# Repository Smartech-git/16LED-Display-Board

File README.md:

# 16LED-Display-Board
16 LEDs display board with 74HC595 SIPO SOIC chips. The two chips are daisy-chained, in effect a plug in and play, creating your electronics art with 16LEDs.

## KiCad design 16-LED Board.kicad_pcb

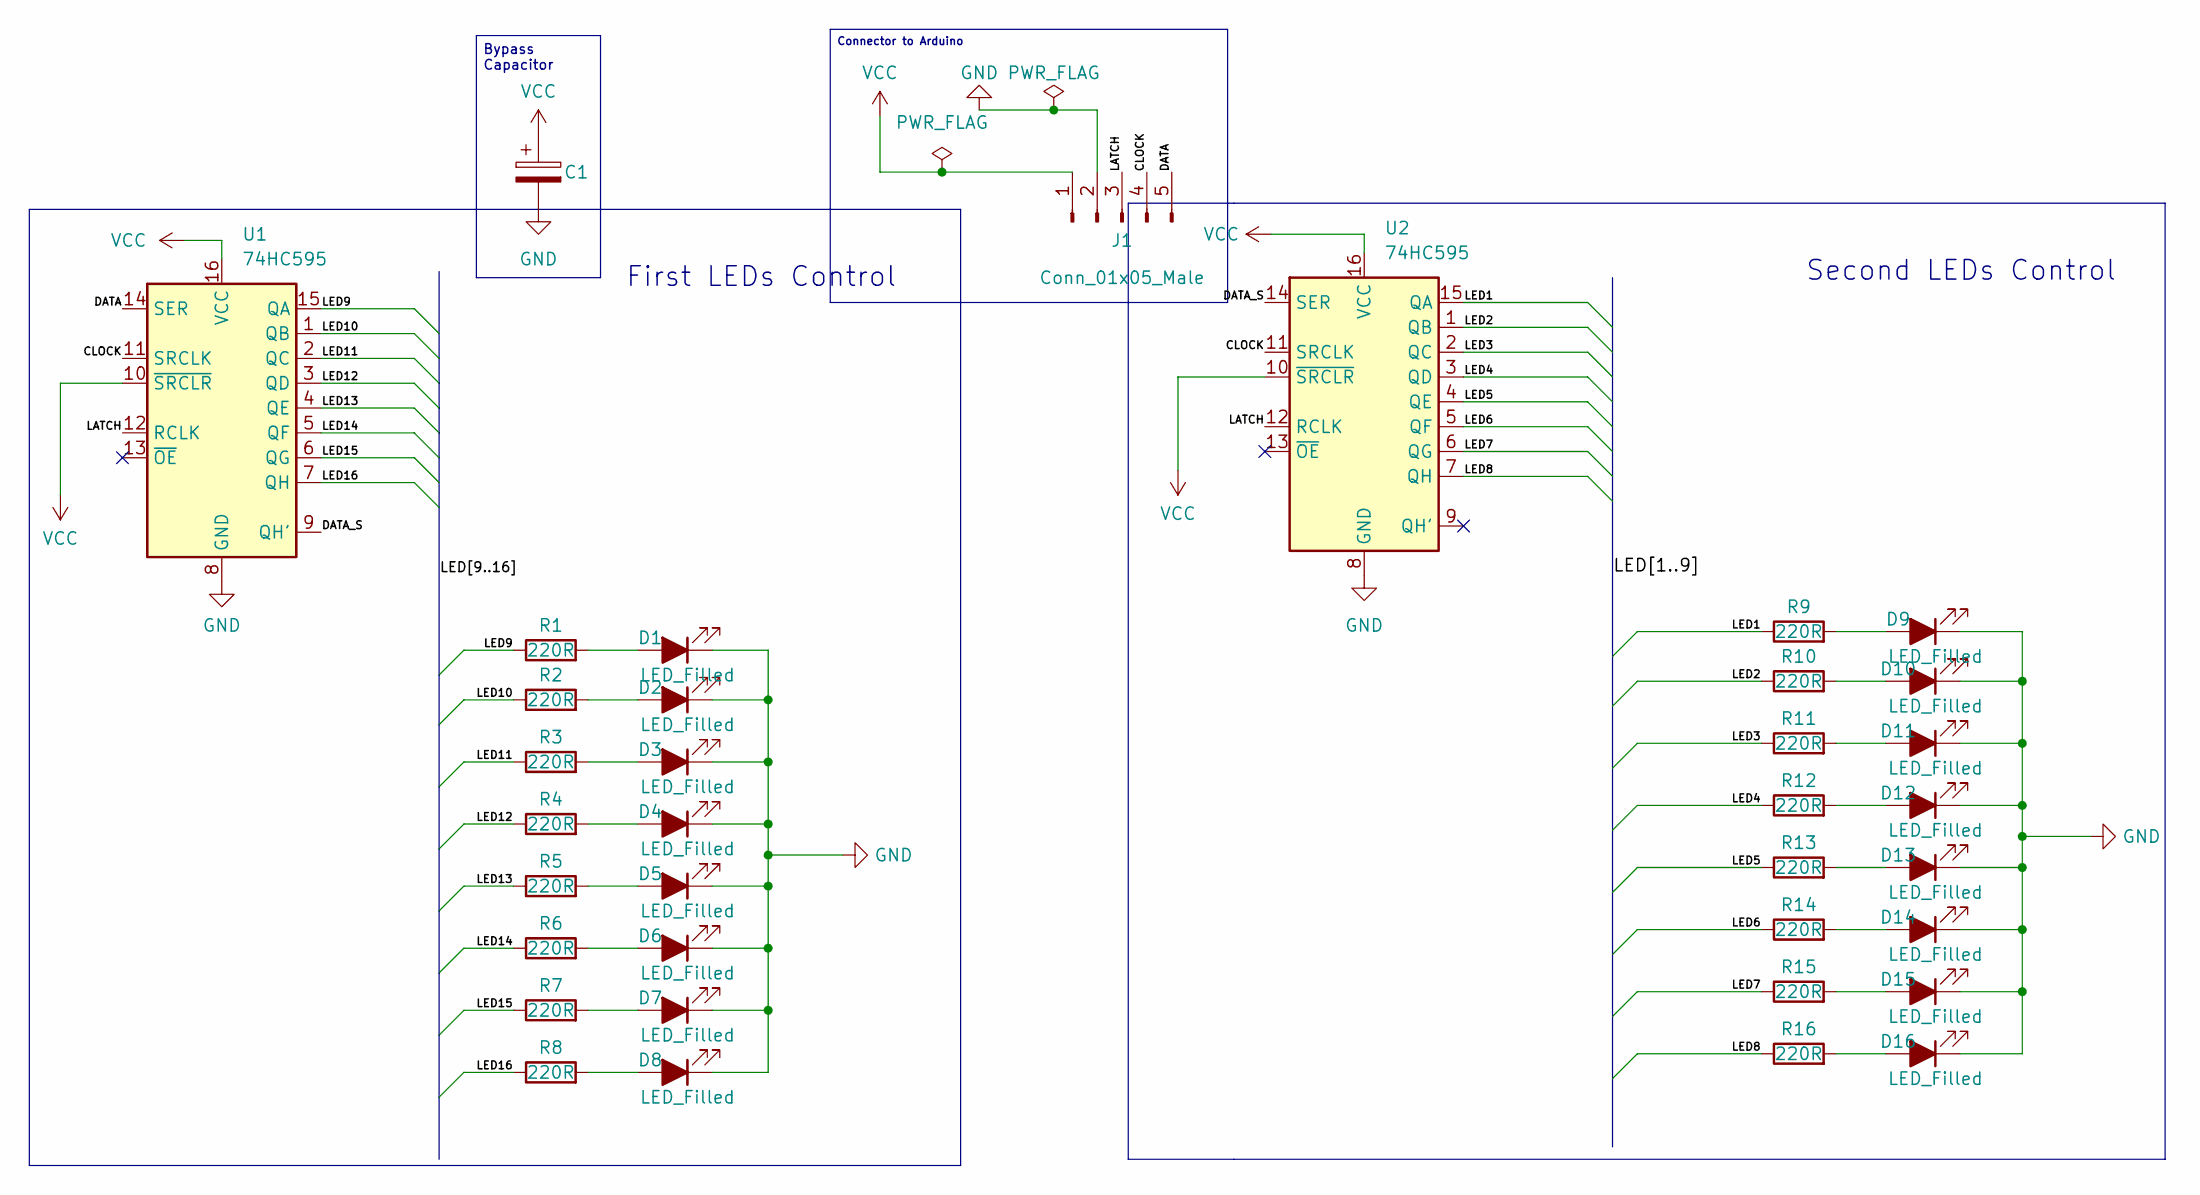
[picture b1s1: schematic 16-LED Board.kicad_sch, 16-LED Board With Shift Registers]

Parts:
C1: CP_Elec_6.3x5.3
D1, D2, D3, D4, D5, D6, D7, D8, D9, D10, D11, D12, D13, D14, D15, D16: LED_Filled; LED_0805_2012Metric_Pad1.15x1.40mm_HandSolder
J1: Conn_01x05_Male; PinHeader_1x05_P2.54mm_Vertical
R1, R2, R3, R4, R5, R6, R7, R8, R9, R10, R11, R12, R13, R14, R15, R16: 220R; R_0805_2012Metric_Pad1.20x1.40mm_HandSolder
U1, U2: 74HC595; SOIC-16_3.9x9.9mm_P1.27mm

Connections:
/CLOCK: J1.4, U1.11 (SRCLK), U2.11 (SRCLK)
/DATA: J1.5, U1.14 (SER)
/DATA_S: U1.9 (QH'), U2.14 (SER)
/LATCH: J1.3, U1.12 (RCLK), U2.12 (RCLK)
/LED1: R9.1, U2.15 (QA)
/LED2: R10.1, U2.1 (QB)
/LED3: R11.1, U2.2 (QC)
/LED4: R12.1, U2.3 (QD)
/LED5: R13.1, U2.4 (QE)
/LED6: R14.1, U2.5 (QF)
/LED7: R15.1, U2.6 (QG)
/LED8: R16.1, U2.7 (QH)
/LED9: R1.1, U1.15 (QA)
/LED10: R2.1, U1.1 (QB)
/LED11: R3.1, U1.2 (QC)
/LED12: R4.1, U1.3 (QD)
/LED13: R5.1, U1.4 (QE)
/LED14: R6.1, U1.5 (QF)
/LED15: R7.1, U1.6 (QG)
/LED16: R8.1, U1.7 (QH)
GND: C1.2, D1.1 (K), D2.1 (K), D3.1 (K), D4.1 (K), D5.1 (K), D6.1 (K), D7.1 (K), D8.1 (K), D9.1 (K), D10.1 (K), D11.1 (K), D12.1 (K), D13.1 (K), D14.1 (K), D15.1 (K), D16.1 (K), J1.2, U1.8 (GND), U2.8 (GND)
unnamed: D1.2 (A), R1.2
unnamed: D2.2 (A), R2.2
unnamed: D4.2 (A), R4.2
unnamed: D5.2 (A), R5.2
unnamed: D9.2 (A), R9.2
unnamed: D11.2 (A), R11.2
unnamed: D12.2 (A), R12.2
unnamed: D13.2 (A), R13.2
unnamed: D3.2 (A), R3.2
unnamed: D6.2 (A), R6.2
unnamed: D7.2 (A), R7.2
unnamed: D8.2 (A), R8.2
unnamed: D10.2 (A), R10.2
unnamed: D14.2 (A), R14.2
unnamed: D15.2 (A), R15.2
unnamed: D16.2 (A), R16.2
VCC: C1.1, J1.1, U1.10 (~SRCLR), U1.16 (VCC), U2.10 (~SRCLR), U2.16 (VCC)

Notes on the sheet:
Second LEDs Control
First LEDs Control
Connector to Arduino
Bypass Capacitor

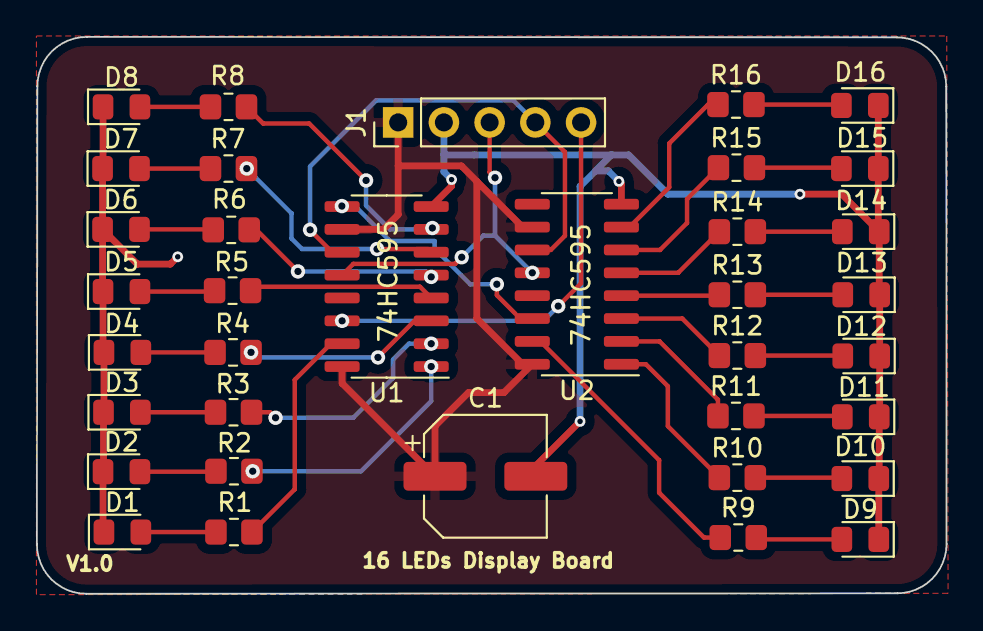
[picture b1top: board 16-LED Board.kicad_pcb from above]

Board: 2 copper layers, 50.5 x 30.9 mm, 36 parts (0 on the bottom side), 38 nets.
